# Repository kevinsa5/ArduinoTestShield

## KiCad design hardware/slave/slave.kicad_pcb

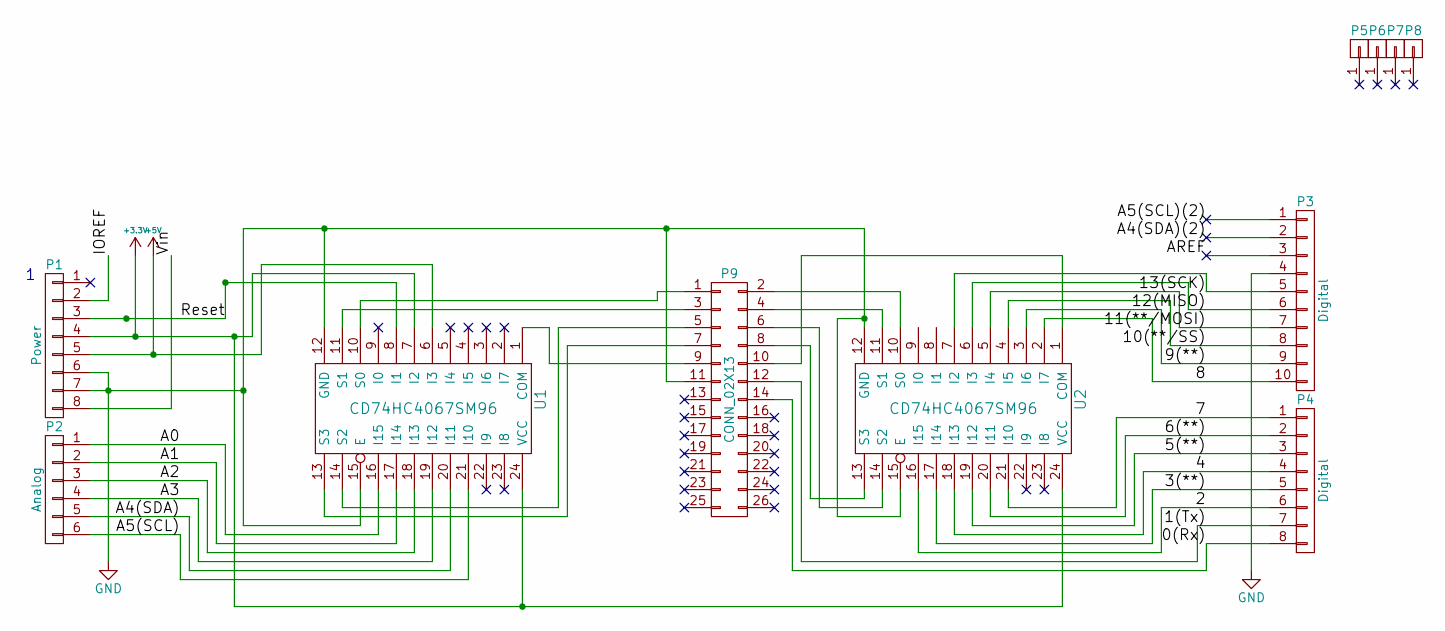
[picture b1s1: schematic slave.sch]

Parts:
P1: Power; Socket_Strip_Arduino_1x08
P2: Analog; Socket_Strip_Arduino_1x06
P3: Digital; Socket_Strip_Arduino_1x10
P4: Digital; Socket_Strip_Arduino_1x08
P5, P6, P7, P8: CONN_01X01; Arduino_1pin
P9: CONN_02X13; Pin_Header_Straight_2x13
U1, U2: CD74HC4067SM96; SOIC-24W_7.5x15.4mm_Pitch1.27mm

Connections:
+3V3: P1.4, U1.7 (I2), U1.24 (VCC), U2.24 (VCC)
+5V: P1.5, U1.6 (I3)
/0(Rx): P4.8, P9.14
/1(Tx): P4.7, P9.12
/2: P4.6, U2.16 (I15)
/3(**): P4.5, U2.17 (I14)
/4: P4.4, U2.18 (I13)
/5(**): P4.3, U2.19 (I12)
/6(**): P4.2, U2.20 (I11)
/7: P4.1, U2.21 (I10)
/8: P3.10, U2.2 (I7)
/9(**): P3.9, U2.3 (I6)
/10(**/SS): P3.8, U2.4 (I5)
/11(**/MOSI): P3.7, U2.5 (I4)
/12(MISO): P3.6, U2.6 (I3)
/13(SCK): P3.5, U2.7 (I2)
/A0: P2.1, U1.16 (I15)
/A1: P2.2, U1.17 (I14)
/A2: P2.3, U1.18 (I13)
/A3: P2.4, U1.19 (I12)
/A4(SDA): P2.5, U1.20 (I11)
/A4(SDA)(2): P3.2
/A5(SCL): P2.6, U1.21 (I10)
/A5(SCL)(2): P3.1
/AREF: P3.3
/IOREF: P1.2
/Reset: P1.3, U1.8 (I1)
/Vin: P1.8
GND: P1.6, P1.7, P3.4, P9.11, U1.12 (GND), U1.15 (E), U2.12 (GND), U2.15 (E)
unnamed: P9.1, U1.10 (S0)
unnamed: P9.2, U2.10 (S0)
unnamed: P9.3, U1.11 (S1)
unnamed: P9.4, U2.11 (S1)
unnamed: P9.5, U1.14 (S2)
unnamed: P9.6, U2.14 (S2)
unnamed: P9.7, U1.13 (S3)
unnamed: P9.8, U2.13 (S3)
unnamed: P9.9, U1.1 (COM)
unnamed: P9.10, U2.1 (COM)

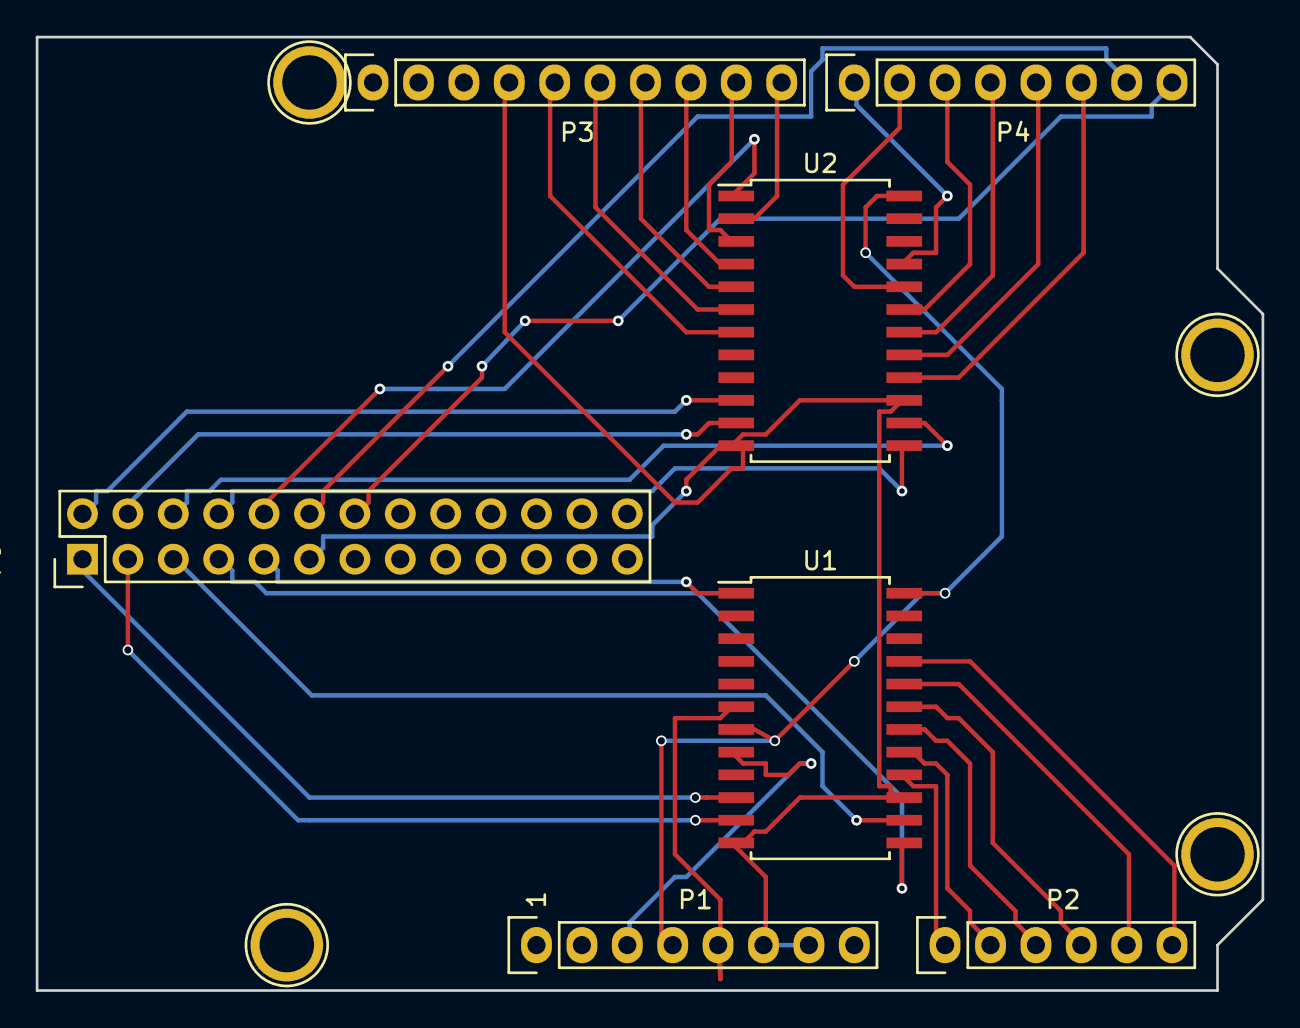
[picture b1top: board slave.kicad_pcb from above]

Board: 2 copper layers, 68.6 x 53.3 mm, 11 parts (0 on the bottom side), 34 nets.

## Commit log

2016-12-26 preliminary sketches and slave board layout
2016-12-26 fixed symlink for ArduinoTestShield.h
